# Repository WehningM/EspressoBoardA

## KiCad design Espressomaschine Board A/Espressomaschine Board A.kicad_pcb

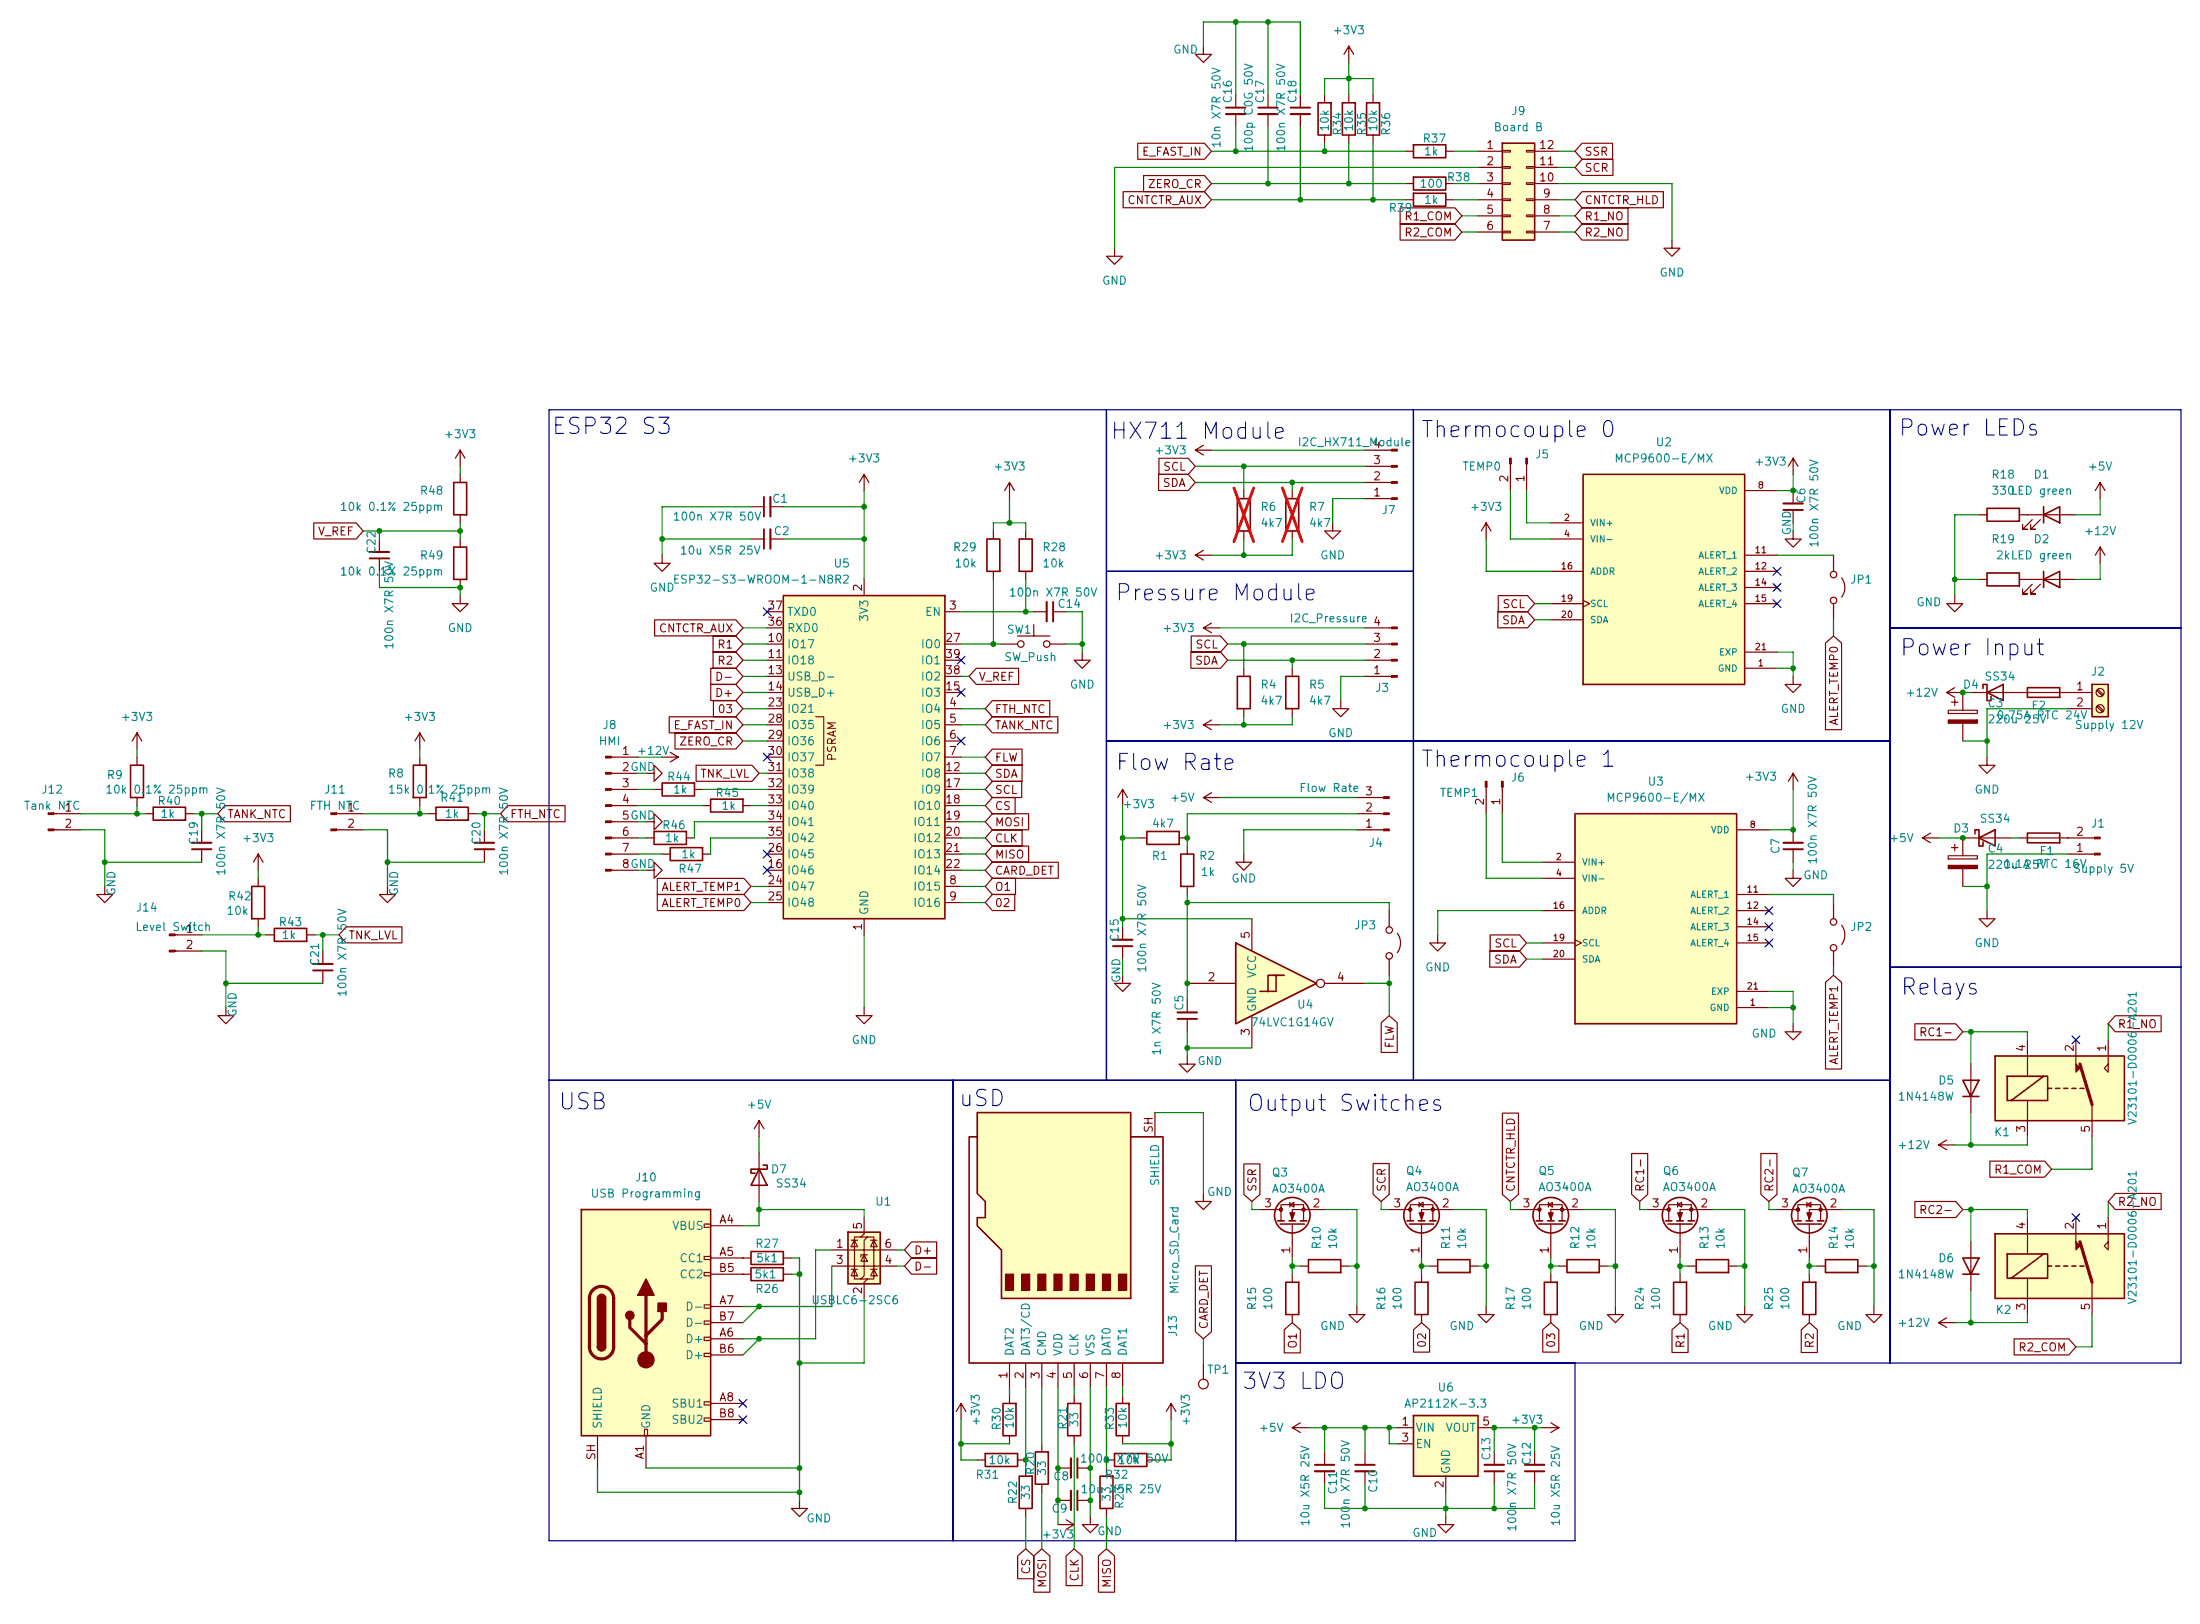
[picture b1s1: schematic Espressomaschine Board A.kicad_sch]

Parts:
C1, C6, C7, C8, C10, C13, C14, C15, C18, C19, C20, C21, C22: 100n X7R 50V; C_0603_1608Metric; MPN CC0603KRX7R9BB104; LCSC C14663
C2, C9, C11, C12: 10u X5R 25V; C_0805_2012Metric_Pad1.18x1.45mm_HandSolder; MPN CL21A106KAYNNNE; LCSC C15850
C3, C4: 220u 25V; CP_Radial_D10.0mm_P3.50mm; MPN 25YXF220MEFC8X11.5
C5: 1n X7R 50V; C_0603_1608Metric; MPN CL10B102KB8NNNC; LCSC C1588
C16: 10n X7R 50V; C_0603_1608Metric; MPN 0603B103K500NT; LCSC C57112
C17: 100p C0G 50V; C_0603_1608Metric; MPN CL10C101JB8NNNC; LCSC C14858
D1, D2: LED green; LED_0805_2012Metric_Pad1.15x1.40mm_HandSolder; MPN KT-0805G; LCSC C2297
D3, D4, D7: SS34; D_SMA_Handsoldering; MPN SS34; LCSC C8678
D5, D6: 1N4148W; D_SOD-123; MPN 1N4148W; LCSC C81598
F1: 1.1A PTC 16V; Fuse_1812_4532Metric; MPN SMD1812P110TF/16
F2: 0.75A PTC 24V; Fuse_1812_4532Metric; MPN SMD1812P075TF/24
J1: Supply 5V; JST_XH_S2B-XH-A-1_1x02_P2.50mm_Horizontal; MPN S2B-XH-A-1(LF)(SN)
J2: Supply 12V; TerminalBlock_MetzConnect_Type011_RT05502HBLC_1x02_P5.00mm_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; MPN KF301-5.0-2P
J3: I2C_Pressure; JST_ZH_B4B-ZR_1x04_P1.50mm_Vertical; MPN B4B-ZR(LF)(SN)
J4: Flow Rate; JST_XH_S3B-XH-A-1_1x03_P2.50mm_Horizontal; MPN S3B-XH-A-1(LF)(SN)
J5: TEMP0; WAGO2060; MPN 2060-452/998-404
J6: TEMP1; WAGO2060; MPN 2060-452/998-404
J7: I2C_HX711_Module; JST_PH_S4B-PH-K_1x04_P2.00mm_Horizontal; MPN S4B-PH-K-S(LF)(SN)
J8: HMI; TE_84952-8_1x08-1MP_P1.0mm_Horizontal; MPN 84952-8
J9: Board B; IDC-Header_2x06_P2.54mm_Horizontal; MPN 2.54-2*6P
J10: USB Programming; USB_C_Receptacle_GCT_USB4105-xx-A_16P_TopMnt_Horizontal; MPN USB4105-GF-A-120
J11: FTH NTC; JST_XH_B2B-XH-A_1x02_P2.50mm_Vertical; MPN B2B-XH-A(LF)(SN)
J12: Tank NTC; JST_XH_B2B-XH-A_1x02_P2.50mm_Vertical; MPN B2B-XH-A(LF)(SN)
J13: Micro_SD_Card; microSD_HC_Hirose_DM3D-SF; MPN DM3D-SF
J14: Level Switch; JST_XH_B2B-XH-A_1x02_P2.50mm_Vertical; MPN B2B-XH-A(LF)(SN)
JP1, JP2, JP3: Jumper_2_Open; SolderJumper-2_P1.3mm_Open_RoundedPad1.0x1.5mm
K1, K2: V23101-D0006-A201; Relay_SPDT_Axicom_W11_V23101-D0xxx-A; MPN V23101-D0006-A201
Q3, Q4, Q5, Q6, Q7: AO3400A; SOT-23; MPN AO3400A; LCSC C20917
R1, R4, R5: 4k7; R_0805_2012Metric_Pad1.20x1.40mm_HandSolder; MPN 0805W8F4701T5E; LCSC C17673
R2, R37, R39, R40, R41, R43, R44, R45, R46, R47: 1k; R_0805_2012Metric_Pad1.20x1.40mm_HandSolder; MPN 0805W8F1001T5E; LCSC C17513
R6, R7: 4k7; R_0805_2012Metric_Pad1.20x1.40mm_HandSolder; MPN 0805W8F4701T5E; not fitted
R8: 15k 0.1% 25ppm; R_0805_2012Metric_Pad1.20x1.40mm_HandSolder; MPN RT0805BRD0715KL
R9, R48, R49: 10k 0.1% 25ppm; R_0805_2012Metric_Pad1.20x1.40mm_HandSolder; MPN RT0805BRD0710KL
R10, R11, R12, R13, R14, R28, R29, R30, R31, R32, R33, R34, R35, R36, R42: 10k; R_0805_2012Metric_Pad1.20x1.40mm_HandSolder; MPN 0805W8F1002T5E; LCSC C17414
R15, R16, R17, R24, R25, R38: 100; R_0805_2012Metric_Pad1.20x1.40mm_HandSolder; MPN 0805W8F1000T5E; LCSC C17408
R18: 330; R_0805_2012Metric_Pad1.20x1.40mm_HandSolder; MPN 0805W8F3300T5E; LCSC C17630
R19: 2k; R_0805_2012Metric_Pad1.20x1.40mm_HandSolder; MPN 0805W8F2001T5E; LCSC C17604
R20, R21, R22, R23: 33; R_0805_2012Metric_Pad1.20x1.40mm_HandSolder; MPN 0805W8F330JT5E; LCSC C17634
R26, R27: 5k1; R_0805_2012Metric_Pad1.20x1.40mm_HandSolder; MPN 0805W8F5101T5E; LCSC C27834
SW1: SW_Push; SW_SPST_EVQP2_MiddlePushTravel_H2.5mm; MPN EVQP2P02W
TP1: TestPoint; TestPoint_Pad_D2.0mm
U1: USBLC6-2SC6; SOT-23-6; MPN USBLC6-2SC6
U2, U3: MCP9600-E/MX; QFN65P500X500X100-21N; PARTREV F
U4: 74LVC1G14GV; SOT-23-5_HandSoldering; MPN 74LVC1G14GV,125
U5: ESP32-S3-WROOM-1-N8R2; ESP32-S3-WROOM-1; MPN ESP32-S3-WROOM-1-N8R2
U6: AP2112K-3.3; SOT-23-5; MPN AP2112K-3.3TRG1

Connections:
02: R16.1, U5.9 (IO16)
03: R17.1, U5.23 (IO21)
+3V3: C1.2, C2.2, C6.2, C7.2, C8.2, C9.2, C12.2, C13.2, C15.2, J3.4, J7.4, J13.4 (VDD), R1.1, R4.2, R5.2, R6.2, R7.2, R8.1, R9.1, R28.1, R29.1, R30.1, R31.2, R32.1, R33.1, R34.2, R35.2, R36.2, R42.1, R48.1, U2.8 (VDD), U2.16 (ADDR), U3.8 (VDD), U4.5 (VCC), U5.2 (3V3), U6.5 (VOUT)
+5V: C4.1, C10.1, C11.1, D1.2 (A), D3.1 (K), D7.1 (K), J4.3, U6.1 (VIN), U6.3 (EN)
+12V: C3.1, D2.2 (A), D4.1 (K), D5.1 (K), D6.1 (K), J8.1, K1.3, K2.3
ALERT_TEMP0: JP1.2 (B), U5.25 (IO48)
ALERT_TEMP1: JP2.2 (B), U5.24 (IO47)
CARD_DET: TP1.1 (1_1), U5.22 (IO14)
CLK: R21.1, U5.20 (IO12)
CNTCTR_AUX: C18.2, R36.1, R39.2, U5.36 (RXD0)
CNTCTR_HLD: J9.9, Q5.3 (D)
CS: R22.1, U5.18 (IO10)
D+: U1.6 (I/O1), U5.14 (USB_D+)
D-: U1.4 (I/O2), U5.13 (USB_D-)
E_FAST_IN: C16.2, R34.1, R37.2, U5.28 (IO35)
FLW: JP3.2 (B), U4.4, U5.7 (IO7)
FTH_NTC: C20.2, R41.2, U5.4 (IO4)
GND: C1.1, C2.1, C3.2, C4.2, C5.1, C6.1, C7.1, C8.1, C9.1, C10.2, C11.2, C12.1, C13.1, C14.1, C15.1, C16.1, C17.1, C18.1, C19.1, C20.1, C21.1, C22.1, J1.1, J2.2, J3.1, J4.1, J7.1, J8.2, J8.5, J8.8, J9.2, J9.10, J10.A1 (GND), J10.A12 (GND), J10.B1 (GND), J10.B12 (GND), J10.SH (SHIELD), J11.2, J12.2, J13.6 (VSS), J13.SH (SHIELD), J14.2, Q3.2 (S), Q4.2 (S), Q5.2 (S), Q6.2 (S), Q7.2 (S), R10.2, R11.2, R12.2, R13.2, R14.2, R18.1, R19.1, R26.2, R27.2, R49.2, SW1.2, U1.2 (GND), U2.1 (GND), U2.3 (GND), U2.5 (GND), U2.6 (GND), U2.7 (GND), U2.9 (GND), U2.10 (GND), U2.13 (GND), U2.17 (GND), U2.18 (GND), U2.21 (EXP), U2.22 (EXP), U2.23 (EXP), U2.24 (EXP), U2.25 (EXP), U2.26 (EXP), U2.27 (EXP), U2.28 (EXP), U2.29 (EXP), U2.30 (EXP), U3.1 (GND), U3.3 (GND), U3.5 (GND), U3.6 (GND), U3.7 (GND), U3.9 (GND), U3.10 (GND), U3.13 (GND), U3.16 (ADDR), U3.17 (GND), U3.18 (GND), U3.21 (EXP), U3.22 (EXP), U3.23 (EXP), U3.24 (EXP), U3.25 (EXP), U3.26 (EXP), U3.27 (EXP), U3.28 (EXP), U3.29 (EXP), U3.30 (EXP), U4.3 (GND), U5.1 (GND), U5.40 (GND), U5.41 (GND), U6.2 (GND)
MISO: R23.1, U5.21 (IO13)
MOSI: R20.1, U5.19 (IO11)
unnamed: D1.1 (K), R18.2
unnamed: D2.1 (K), R19.2
unnamed: D3.2 (A), F1.1
unnamed: D4.2 (A), F2.1
unnamed: D7.2 (A), J10.A4 (VBUS), J10.A9 (VBUS), J10.B4 (VBUS), J10.B9 (VBUS), U1.5 (VBUS)
unnamed: F1.2, J1.2
unnamed: F2.2, J2.1
unnamed: J4.2, R1.2, R2.1
unnamed: J5.1, U2.2 (VIN+)
unnamed: J5.2, U2.4 (VIN-)
unnamed: J6.1, U3.2 (VIN+)
unnamed: J6.2, U3.4 (VIN-)
unnamed: J8.3, R44.1
unnamed: J8.4, R45.1
unnamed: J8.6, R46.1
unnamed: J8.7, R47.1
unnamed: J9.1, R37.1
unnamed: J9.3, R38.1
unnamed: J9.4, R39.1
unnamed: J10.A5 (CC1), R27.1
unnamed: J10.B5 (CC2), R26.1
unnamed: J10.A6 (D+), J10.B6 (D+), U1.1 (I/O1)
unnamed: J10.A7 (D-), J10.B7 (D-), U1.3 (I/O2)
unnamed: J11.1, R8.2, R41.1
unnamed: J12.1, R9.2, R40.1
unnamed: J13.5 (CLK), R21.2
unnamed: J13.3 (CMD), R20.2
unnamed: J13.7 (DAT0), R23.2, R32.2
unnamed: J13.8 (DAT1), R33.2
unnamed: J13.1 (DAT2), R30.2
unnamed: J13.2 (DAT3/CD), R22.2, R31.1
unnamed: J14.1, R42.2, R43.1
unnamed: JP1.1 (A), U2.11 (ALERT_1)
unnamed: JP2.1 (A), U3.11 (ALERT_1)
unnamed: C5.2, JP3.1 (A), R2.2, U4.2
unnamed: Q3.1 (G), R10.1, R15.2
unnamed: Q4.1 (G), R11.1, R16.2
unnamed: Q5.1 (G), R12.1, R17.2
unnamed: Q6.1 (G), R13.1, R24.2
unnamed: Q7.1 (G), R14.1, R25.2
unnamed: C14.2, R28.2, U5.3 (EN)
unnamed: R29.2, SW1.1, U5.27 (IO0)
unnamed: R44.2, U5.32 (IO39)
unnamed: R45.2, U5.33 (IO40)
unnamed: R46.2, U5.34 (IO41)
unnamed: R47.2, U5.35 (IO42)
O1: R15.1, U5.8 (IO15)
R1: R24.1, U5.10 (IO17)
R1_COM: J9.5, K1.5, K1.6
R1_NO: J9.8, K1.1
R2: R25.1, U5.11 (IO18)
R2_COM: J9.6, K2.5, K2.6
R2_NO: J9.7, K2.1
RC1-: D5.2 (A), K1.4, Q6.3 (D)
RC2-: D6.2 (A), K2.4, Q7.3 (D)
SCL: J3.3, J7.3, R4.1, R6.1, U2.19 (SCL), U3.19 (SCL), U5.17 (IO9)
SCR: J9.11, Q4.3 (D)
SDA: J3.2, J7.2, R5.1, R7.1, U2.20 (SDA), U3.20 (SDA), U5.12 (IO8)
SSR: J9.12, Q3.3 (D)
TANK_NTC: C19.2, R40.2, U5.5 (IO5)
TNK_LVL: C21.2, R43.2, U5.31 (IO38)
V_REF: C22.2, R48.2, R49.1, U5.38 (IO2)
ZERO_CR: C17.2, R35.1, R38.2, U5.29 (IO36)

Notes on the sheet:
ESP32 S3
Power LEDs
USB
Thermocouple 0
HX711 Module
Output Switches
3V3 LDO
uSD
Power Input
Flow Rate
Thermocouple 1
Pressure Module
Relays

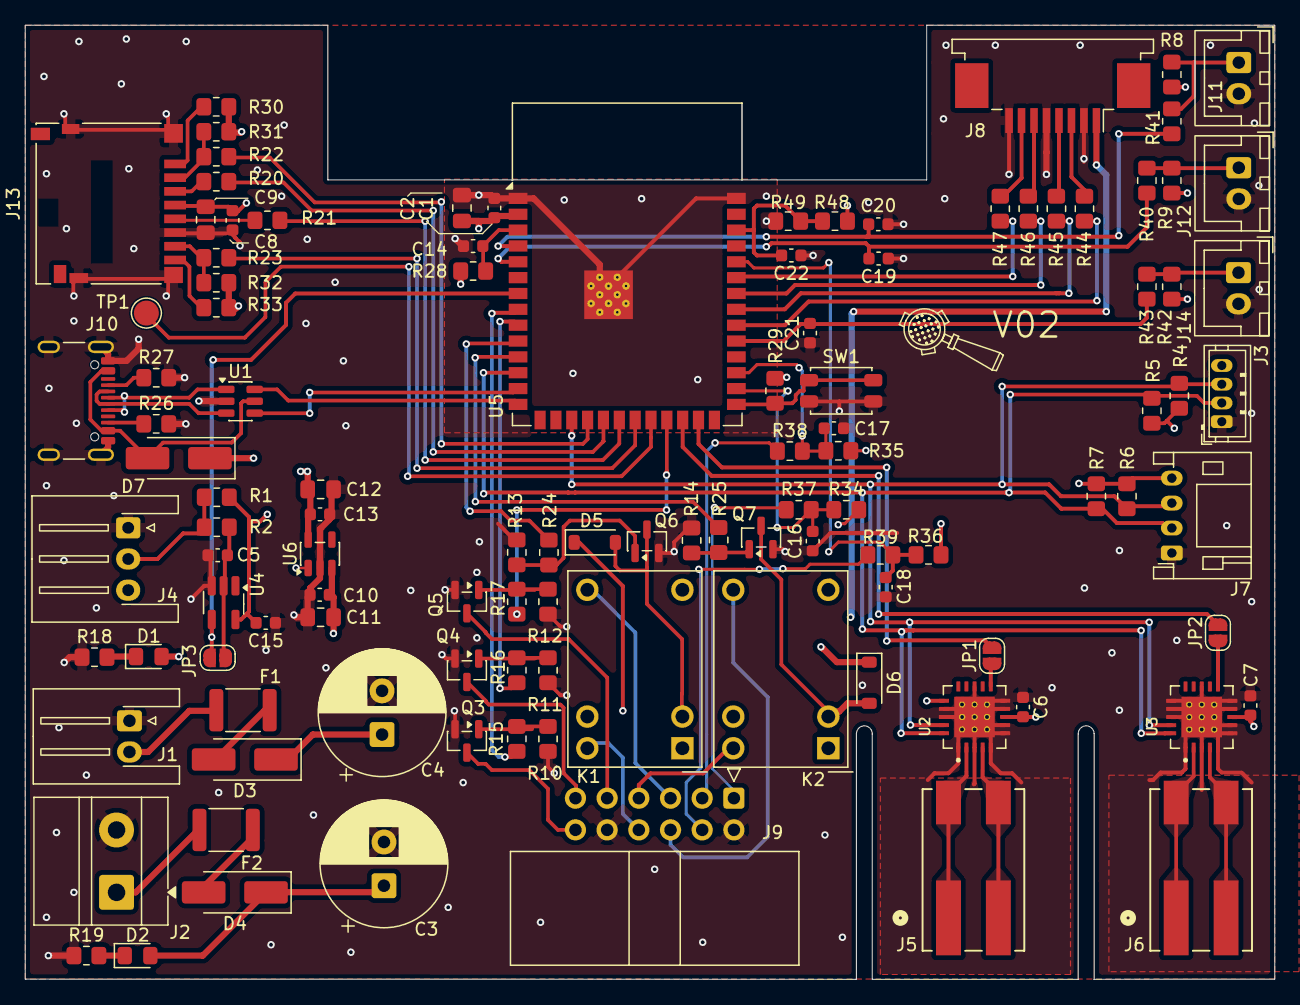
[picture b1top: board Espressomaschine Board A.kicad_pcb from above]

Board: 4 copper layers, 100.2 x 76.5 mm, 111 parts (0 on the bottom side), 83 nets.
